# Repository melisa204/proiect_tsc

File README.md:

# TSC-Project

## BOM (Bill Of Materials)

| Component  | Supplier Link | Datasheet |
|------------|---------------|-----------|
| 112A-TAAR-R03 | [Model](https://store.comet.srl.ro/Catalogue/Product/43497/) | [Datasheet](https://www.snapeda.com/parts/112A-TAAR-R03/Attend/datasheet/) |
| 744043680 | [Model](https://ro.mouser.com/ProductDetail/Wurth-Elektronik/744043680?qs=PGXP4M47uW6VkZq%252BkzjrHA%3D%3D) | [Datasheet](https://www.we-online.com/components/products/datasheet/744043680.pdf) |
| BD5229G-TR | [Model](https://componentsearchengine.com/part-view/BD5229G-TR/ROHM%20Semiconductor) | [Datasheet](https://fscdn.rohm.com/en/products/databook/datasheet/ic/power/voltage_detector/bd52xxg-e.pdf) |
| Capacitor 0402 | [Model](https://ro.mouser.com/c/passive-components/capacitors/ceramic-capacitors/?q=CC0402&srsltid=AfmBOoogjqwwed3xvp6V5-bfVkRuawirfMcnAC47L-UQdC3mnXJk097M) | [Datasheet](https://componentsearchengine.com/Datasheets/2/CC0402MRX5R5BB106.pdf) |
| CPH3225A | [Model](https://www.snapeda.com/parts/CPH3225A/Seiko+Instruments/view-part/?ref=snap) | [Datasheet](https://www.snapeda.com/parts/CPH3225A/Seiko%20Instruments/datasheet/) |
| Custom Button | [Model](https://industry.panasonic.com/global/en/products/control/switch/light-touch/number/evqpuj02k) | [Datasheet](https://industry.panasonic.com/global/en/downloads?tab=catalog&small_g_cd=203&part_no=EVQPUJ02K) |
| DS3231SN | [Model](https://www.snapeda.com/parts/DS3231SN%23/Analog+Devices/view-part/?ref=eda) | [Datasheet](https://www.snapeda.com/parts/DS3231SN%23/Analog%20Devices/datasheet/) |
| ESP32 WROVER 0805 Capacitor | [Model](https://componentsearchengine.com/part-view/SD0805S020S1R0/Kyocera%20AVX) | [Datasheet]() |
| ESP32 WROVER BME680 Sensor | [Model](https://www.snapeda.com/parts/BME680/Bosch/view-part/?welcome=home) | [Datasheet](https://www.bosch-sensortec.com/media/boschsensortec/downloads/datasheets/bst-bme680-ds001.pdf) |
| ESP32 WROVER MCP73831 Power Management | [Model](https://www.snapeda.com/parts/BME680/Bosch/view-part/?welcome=home) | [Datasheet](https://www.snapeda.com/parts/MCP73831T-2ACI/OT/Microchip/datasheet/) |
| ESP32C6 Varistor 1812 | [Model](https://ro.mouser.com/ProductDetail/EPCOS-TDK/B72520T0350K062?qs=dEfas%2FXlABIszF52uu7vrg%3D%3D) | [Datasheet](https://ro.mouser.com/ProductDetail/EPCOS-TDK/B72520T0350K062?qs=dEfas%2FXlABIszF52uu7vrg%3D%3D&srsltid=AfmBOoq4QYIa9SsFxPeCqCK4SAxNo8l_QYsiO3XkER-r9cuptx7tEupO) |
| ESP32C6 WROOM-1-N8| [Model](https://www.snapeda.com/parts/ESP32-C6-WROOM-1-N8/Espressif+Systems/view-part/?ref=eda) | [Datasheet](https://www.snapeda.com/parts/ESP32-C6-WROOM-1-N8/Espressif%20Systems/datasheet/) |
| FH34SRJ-24S-0.5SH | [Model](https://ro.mouser.com/ProductDetail/Hirose-Connector/FH34SRJ-24S-0.5SH99?qs=vcbW%252B4%252BSTIpKBl5ap9J8Fw%3D%3D) | [Datasheet](https://www.snapeda.com/parts/FH34SRJ-24S-0.5SH(99)/Hirose%20Connector/datasheet/) |
| LED Chip 0603 | [Model](https://www.snapeda.com/parts/KP-1608SURCK/Kingbright/view-part/?ref=search&t=LED%200603) | [Datasheet](https://www.snapeda.com/parts/KP-1608SURCK/Kingbright/datasheet/) |
| MAX17048G+T10 | [Model](https://www.snapeda.com/parts/MAX17048G+T10/Analog+Devices/view-part/?ref=eda) | [Datasheet](https://www.snapeda.com/parts/MAX17048G+T10/Analog%20Devices/datasheet/) |
| MBR0530 Schottky Diode | [Model](https://www.snapeda.com/parts/MBR0530/Onsemi/view-part/?ref=snap) | [Datasheet](https://www.snapeda.com/parts/MBR0530/ON%20Semiconductor/datasheet/) |
| PGB1010603MR | [Model](https://www.snapeda.com/parts/PGB1010603MR/Littelfuse/view-part/?ref=eda) | [Datasheet](https://www.snapeda.com/parts/PGB1010603MR/Littelfuse%20Inc./datasheet/) |
| QWIIC Connector | [Model](https://www.snapeda.com/parts/PRT-14417/SparkFun/view-part/) | [Datasheet](https://www.snapeda.com/parts/PRT-14417/SparkFun%20Electronics/datasheet/) |
| RCL CPOL 3528 | [Model](https://www.snapeda.com/parts/CPH3225A/Seiko+Instruments/view-part/?ref=eda) | [Datasheet](https://s3.amazonaws.com/snapeda/datasheet/TAJB475K025RNJ_AVX.pdf) |
| Resistor 0402 | [Model](https://grabcad.com/library/resistor-0402-1) | [Datasheet](https://www.yageo.com/upload/media/product/products/datasheet/rchip/PYu-RC_Group_51_RoHS_L_12.pdf) |
| SI1308EDL-T1-GE3 MOSFET | [Model](https://www.snapeda.com/parts/SI1308EDL-T1-GE3/Vishay+Siliconix/view-part/?welcome=home&ref=eda) | [Datasheet](https://www.snapeda.com/parts/SI1308EDL-T1-GE3/Vishay%20Siliconix/datasheet/) |
| SJ | [Model](https://grabcad.com/library/solder-jumpers-1) | [Datasheet]() |
| USB4110-GF-A | [Model](https://componentsearchengine.com/part-view/USB4110-GF-A/GCT%20(GLOBAL%20CONNECTOR%20TECHNOLOGY)) | [Datasheet](https://gct.co/files/drawings/usb4110.pdf) |
| USBLC6-2SC6Y | [Model](https://www.snapeda.com/parts/USBLC6-2SC6Y/STMicroelectronics/view-part/?welcome=home&ref=eda) | [Datasheet](https://www.snapeda.com/parts/USBLC6-2SC6Y/STMicroelectronics/datasheet/) |
| W25Q512JVEIQ | [Model](https://www.snapeda.com/parts/W25Q512JVEIQ/Winbond+Electronics/view-part/?ref=eda) | [Datasheet](https://www.winbond.com/resource-files/W25Q512JV%20SPI%20RevB%2006252019%20KMS.pdf) |
| XC6220A331MR-G | [Model](https://componentsearchengine.com/part-view/XC6220A331MR-G/Torex) | [Datasheet](https://product.torexsemi.com/system/files/series/xc6220.pdf) |

## Power Consumption Estimation

## Hardware Description  

1. Microcontroller – ESP32-C6-WROOM-1-N8
The ESP32-C6 serves as the main processing unit, managing overall system operations, interfacing with
sensors and external modules, and overseeing power management tasks.
Architecture: 32-bit RISC-V
Clock Speed: 160 MHz
Wireless Connectivity: Wi-Fi 6 (2.4 GHz), Bluetooth 5.0

3. Power Management & Battery Battery Type: Li-Po (Lithium Polymer)
Capacity: 3.7V, 1800mAh
Charging Circuit: MCP73831T
Input Voltage: 5V via USB-C
Protection Features: Overcharge and deep discharge protection
Voltage Regulator: LDO regulator ensures a stable 3.3V power supply to all components.

4. Display - E-Paper (E-Ink) Screen
Size: 7.5 inches
Resolution: 800x480 pixels
Communication Interface: SPI

5. SD Card Module
Type: MicroSD (Supports FAT32)
Interface: SPI

6. External NOR Flash
Capacity: 64MB
Interface: SPI

7. Environmental Sensor - BME688
Functions: Measures temperature, humidity, air pressure, and gas levels.
Communication Interface: I2C 

8. Real-Time Clock (RTC) - DS3231SN
Functionality: Maintains time and date even when the system is powered off.
Communication Interface: I2C 

9. USB-C Connector & ESD Protection
Functionality: Provides power input and data transfer capability.
Protection: Integrated ESD protection and Schottky diode for reverse polarity safety. 

10. Buttons & User Input
Tactile Push Buttons

11. Communication Interfaces
GPIO: Used for button controls and general I/O operations.
SPI: Used for SD card, external flash memory, and e-paper display.
I2C: Used for the BME688 environmental sensor and DS3231SN RTC module.
UART: Used for debugging and serial communication.
Wi-Fi & Bluetooth: Provided by ESP32-C6, allowing wireless connectivity.

## Power Consumption Estimation

| Component                | Current Draw (mA) | Voltage (V) | Power (mW) |
|--------------------------|------------------|-------------|------------|
| ESP32-C6 (Wi-Fi active)  |200               |3.3          |660
| E-Paper Display (Updating)               | 40               | 3.3         | 132        |
| BME688 Sensor (Measuring)| 3.1              | 3.3         | 10.23      |
| RTC Module (Active)      | 0.15             | 3.3         | 0.495      |
| SD Card (Active)         | 50               | 3.3         | 165        |
| Externar NOR Flash       | 25               | 3.3         | 82.5       |
| Total Estimated Power Consumption               | ~318.5mA         | 3.3         | 1050.72    |

## ESP32-C6 Pin Mapping  

| Component                | ESP32-C6 Pin(s) | Interface | Purpose |
|--------------------------|----------------|-----------|---------|
| **E-Paper Display**      | IO7 (MOSI), IO6 (SCK), IO10 (CS), IO5 (DC), IO23 (RST), IO3 (BUSY) | SPI | Transfers image data to the display and controls its state. |
| **MicroSD Card**         | IO7 (MOSI), IO6 (SCK), IO4 (SS_SD), IO2 (MISO) | SPI | Allows storage and retrieval of e-book files. |
| **Environmental Sensor (BME688)** | IO21 (SDA), IO22 (SCL) | I2C | Reads temperature, humidity, pressure, and air quality data. |
| **RTC Module (DS3231)**  | IO21 (SDA), IO22 (SCL), IO18 (RST), IO1 (32KHz), IO0 (INT_RTC) | I2C | Keeps track of time even when ESP32 is off. |
| **External NOR Flash**   | IO11 (CS), IO6 (SCK), IO2 (MISO), IO7 (MOSI) | SPI | Provides additional storage for application data. |
| **Battery Monitoring**   | IO21 (SDA), IO22 (SCL) | I2C | Reads battery voltage and charge status. |
| **USB-C Connection**     | GPIOs through voltage regulation | USB | Powers and programs the ESP32-C6. |
| **Control Buttons**      | IO9 (BOOT), IO15 (CHANGE), EN (RESET) | GPIO | User input for device interactions. |
|

## Additional Design Notes
### Footprint Adjustments
Diode (SMD-Hole): The original footprint had pad holes that were too small, which would have caused soldering issues.
The pad size was updated to 35mil x 190mil to ensure manufacturability and a reliable electrical connection.

U4 – MAX17048G+T10: The VBAT power trace was designed with a width of 0.3mm, based on implementation constraints
However, the footprint had pin widths of only 0.27mm, resulting in asymmetry and inconsistent routing. The pin sizes
were adjusted to match the trace width and maintain design symmetry.

### Routing & Ground Plane
Power traces were routed only on the top layer, which required the use of approximately 110 vias to allow for
signal routing on the bottom layer.

The ground plane (GND) was added after routing was completed, applied to both top and bottom layers to ensure
low-impedance grounding and reduced EMI.

### Component Placement
Test pads (TPs) were placed near the edges of the board and close to major components for easy debugging access.

### Schematic & 3D Model Issues
After completing the routing process, updates to the 3D models led to pin order reversals in certain 2-pin components, 
which disrupted existing connections. The issue was resolved by rotating the affected components 180° and re-aligning their 
pins accordingly.

### Enclosure & 3D Integration
3D components were imported using two methods, depending on how frequently each part appeared in the schematic.

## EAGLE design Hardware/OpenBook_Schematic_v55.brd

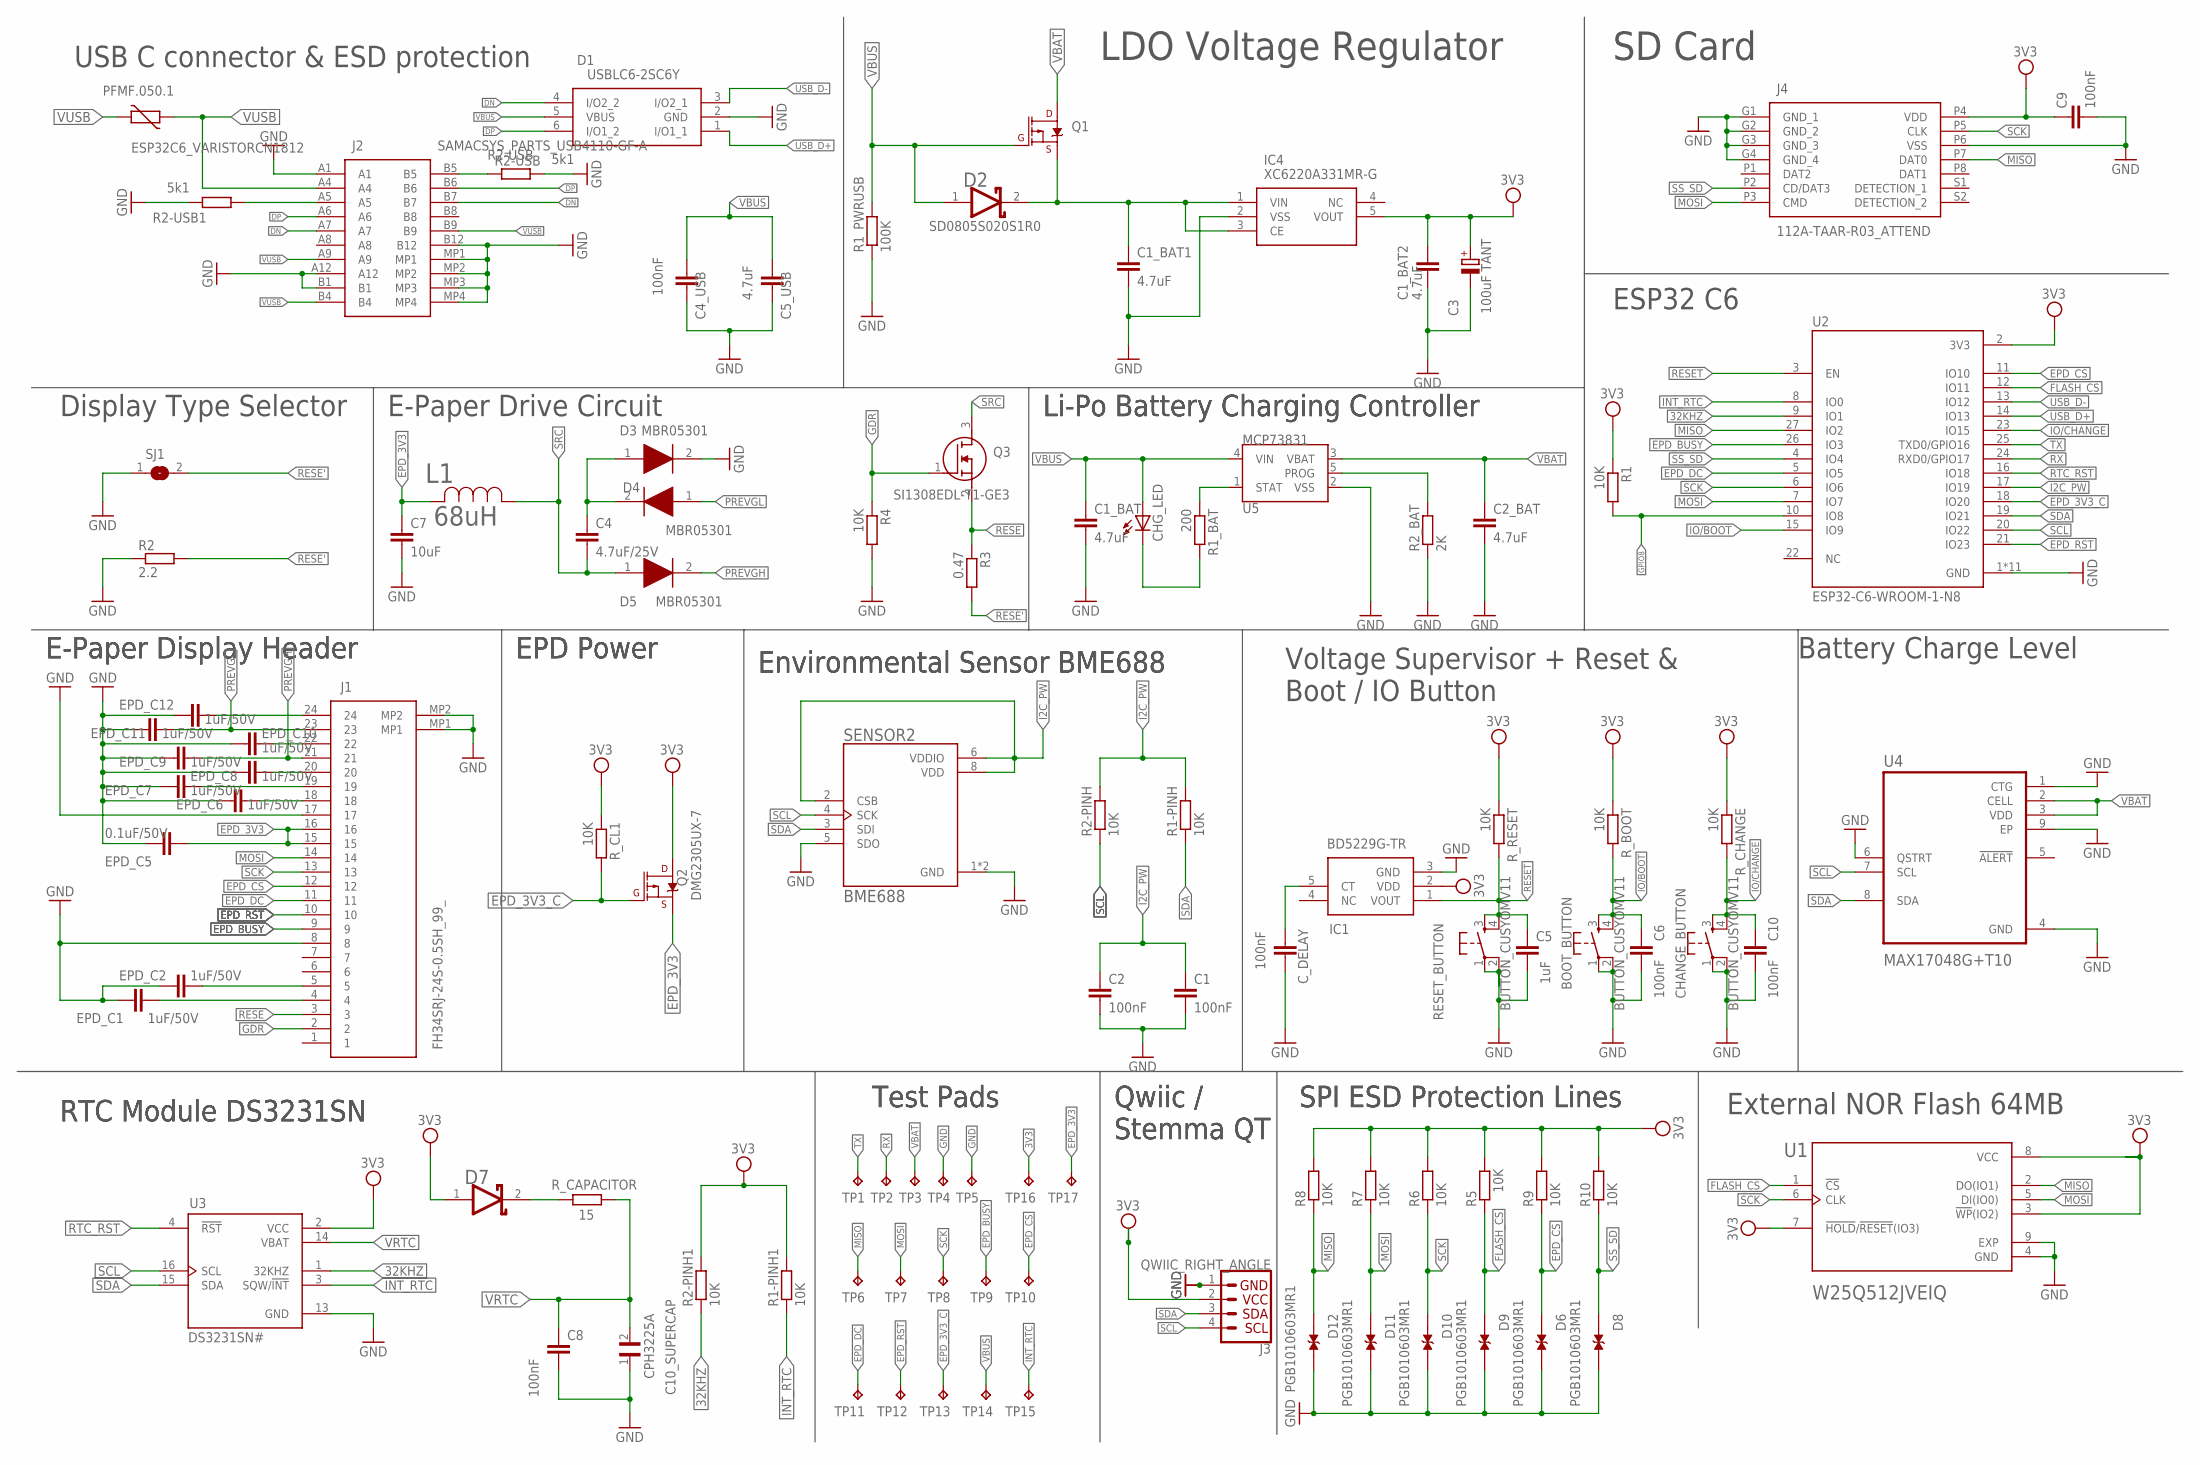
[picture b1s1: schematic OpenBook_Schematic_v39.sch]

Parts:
BOOT_BUTTON: BUTTON_CUSYOMV11; MYBUTTON
C1, C2, C4_USB, C6, C8, C9, C10: 100nF; EAGLE-LTSPICE_C0402
C1_BAT, C1_BAT1, C1_BAT2, C2_BAT, C5_USB: 4.7uF; EAGLE-LTSPICE_C0402
C3: 100uF TANT; RCL_CT3528
C4: 4.7uF/25V; EAGLE-LTSPICE_C0402
C5: 1uF; EAGLE-LTSPICE_C0402
C7: 10uF; EAGLE-LTSPICE_C0402
C10_SUPERCAP: CPH3225A; CAPCP3225X100N
CHANGE_BUTTON: BUTTON_CUSYOMV11; MYBUTTON
CHG_LED: ADAFRUIT_LEDCHIP-LED0603; ADAFRUIT_CHIP-LED0603
C_DELAY: 100nF; EAGLE-LTSPICE_C0402
D1: USBLC6-2SC6Y; SOT95P280X145-6N
D2, D7: SD0805S020S1R0; ESP32_WROVER_AVX---SD0805S020S1R0_AVX_SD0805S020S1R0_0
D3, D4, D5: MBR05301; SOD3716X135N
D6, D8, D9, D10, D11, D12: PGB1010603MR1; DIOC1608X36N
EPD_C1, EPD_C2, EPD_C6, EPD_C7, EPD_C8, EPD_C9, EPD_C10, EPD_C11, EPD_C12: 1uF/50V; EAGLE-LTSPICE_C0402
EPD_C5: 0.1uF/50V; EAGLE-LTSPICE_C0402
IC1: BD5229G-TR; SOT95P280X125-5N
IC4: XC6220A331MR-G; SOT95P280X120-5N
J1: FH34SRJ-24S-0.5SH_99_; FH34SRJ24S05SH99
J2: SAMACSYS_PARTS_USB4110-GF-A; SAMACSYS_PARTS_USB4110GFA
J3: QWIIC_RIGHT_ANGLE; JST04_1MM_RA
J4: 112A-TAAR-R03_ATTEND; 112ATAARR03ATTEND
L1: 68uH; IND_4828-WE-TPC_WRE
PFMF.050.1: ESP32C6_VARISTORCN1812; ESP32C6_VARISTOR_CT/CN1812
Q1, Q2: 20V/4.2A/52mΩ/1.4W; ESP32_WROVER_SPARKFUN-DISCRETESEMI_SOT23-3
Q3: SI1308EDL-T1-GE3; SOT65P210X110-3N
R1, R1-PINH, R1-PINH1, R2-PINH, R2-PINH1, R4, R5, R6, R7, R8, R9, R10: 10K; ESP32_WROVER_EAGLE-LTSPICE_R0402
R1_BAT: 200; ESP32_WROVER_EAGLE-LTSPICE_R0402
R1_PWRUSB: 100K; ESP32_WROVER_EAGLE-LTSPICE_R0402
R2: 2.2; ESP32_WROVER_EAGLE-LTSPICE_R0402
R2-USB, R2-USB1: 5k1; ESP32_WROVER_EAGLE-LTSPICE_R0402
R2_BAT: 2K; ESP32_WROVER_EAGLE-LTSPICE_R0402
R3: 0.47; ESP32_WROVER_EAGLE-LTSPICE_R0402
RESET_BUTTON: BUTTON_CUSYOMV11; MYBUTTON
R_BOOT: 10K; ESP32_WROVER_EAGLE-LTSPICE_R0402
R_CAPACITOR: 15; ESP32_WROVER_EAGLE-LTSPICE_R0402
R_CHANGE: 10K; ESP32_WROVER_EAGLE-LTSPICE_R0402
R_CL1: 10K; ESP32_WROVER_EAGLE-LTSPICE_R0402
R_RESET: 10K; ESP32_WROVER_EAGLE-LTSPICE_R0402
SENSOR2: BME688; ESP32_WROVER_BME680_PSON80P300X300X100-8N
SJ1: SJ
TP1, TP2, TP3, TP4, TP5, TP6, TP7, TP8, TP9, TP10, TP11, TP12, TP13, TP14, TP15, TP16, TP17: TPTP20R; TP20R
U1: W25Q512JVEIQ; SON127P600X800X80-9N
U2: ESP32-C6-WROOM-1-N8; XCVR_ESP32-C6-WROOM-1-N8
U3: DS3231SN#; SOIC127P1032X265-16N
U4: MAX17048G+T10; SON50P200X200X80-9N
U5: MCP73831; ESP32_WROVER_SPARKFUN-IC-POWER_SOT23-5

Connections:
3V3: C1_BAT2.1, C3.+, C9.1, D7.1 (ANODE), IC1.2 (VDD), IC4.5 (VOUT), J3.2, J4.P4 (VDD), Q2.1 (D), R1.1, R1-PINH1.2, R2-PINH1.2, R5.2, R6.2, R7.2, R8.2, R9.2, R10.2, R_BOOT.1, R_CHANGE.1, R_CL1.1, R_RESET.1, TP16.TP, U1.3 (!WP!(IO2)), U1.7 (!HOLD!/!RESET!(IO3)), U1.8 (VCC), U2.2 (3V3), U3.2 (VCC)
32KHZ: R2-PINH1.1, U2.9 (IO1), U3.1 (32KHZ)
DN: D1.4 (I/O2_2), J2.A7, J2.B7
DP: D1.6 (I/O1_2), J2.A6, J2.B6
EPD_3V3: C7.1, EPD_C5.1, J1.15, J1.16, L1.2, Q2.3 (S), TP17.TP
EPD_3V3_C: Q2.2 (G), R_CL1.2, TP13.TP, U2.18 (IO20)
EPD_BUSY: J1.9, TP9.TP, U2.26 (IO3)
EPD_CS: D6.1, J1.12, R9.1, TP10.TP, U2.11 (IO10)
EPD_DC: J1.11, TP11.TP, U2.5 (IO5)
EPD_RST: J1.10, TP12.TP, U2.21 (IO23)
FLASH_CS: D9.1, R5.1, U1.1 (!CS), U2.12 (IO11)
GDR: J1.2, Q3.1 (G), R4.1
GND: BOOT_BUTTON.1, BOOT_BUTTON.2, C1.2, C1_BAT.2, C1_BAT1.2, C1_BAT2.2, C2.2, C2_BAT.2, C3.-, C4_USB.2, C5.2, C5_USB.2, C6.2, C7.2, C8.2, C9.2, C10.2, C10_SUPERCAP.1, CHANGE_BUTTON.1, CHANGE_BUTTON.2, C_DELAY.2, D1.2 (GND), D3.2 (K), D6.2, D8.2, D9.2, D10.2, D11.2, D12.2, EPD_C1.2, EPD_C2.2, EPD_C5.2, EPD_C6.2, EPD_C7.2, EPD_C8.2, EPD_C9.2, EPD_C10.2, EPD_C11.2, EPD_C12.2, IC1.3 (GND), IC4.2 (VSS), J1.8, J1.17, J1.MP1, J1.MP2, J2.A1, J2.A12, J2.B1, J2.B12, J2.MP1, J2.MP2, J2.MP3, J2.MP4, J3.1, J4.G1 (GND_1), J4.G2 (GND_2), J4.G3 (GND_3), J4.G4 (GND_4), J4.P6 (VSS), R1_PWRUSB.1, R2.1, R2-USB.2, R2-USB1.1, R2_BAT.1, R4.2, RESET_BUTTON.1, RESET_BUTTON.2, SENSOR2.1 (GND), SENSOR2.5 (SDO), SENSOR2.7 (GND), SJ1.1, TP4.TP, TP5.TP, U1.4 (GND), U1.9 (EXP), U2.1 (GND), U2.28 (GND), U2.29_1 (GND), U2.29_2 (GND), U2.29_3 (GND), U2.29_4 (GND), U2.29_5 (GND), U2.29_6 (GND), U2.29_7 (GND), U2.29_8 (GND), U2.29_9 (GND), U3.13 (GND), U4.1 (CTG), U4.4 (GND), U4.6 (QSTRT), U4.9 (EP), U5.2 (VSS)
GPIO8: R1.2, U2.10 (IO8)
I2C_PW: C1.1, C2.1, R1-PINH.2, R2-PINH.2, SENSOR2.2 (CSB), SENSOR2.6 (VDDIO), SENSOR2.8 (VDD), U2.17 (IO19)
INT_RTC: R1-PINH1.1, TP15.TP, U2.8 (IO0), U3.3 (SQW/!INT)
IO/BOOT: BOOT_BUTTON.3, BOOT_BUTTON.4, C6.1, R_BOOT.2, U2.15 (IO9)
IO/CHANGE: C10.1, CHANGE_BUTTON.3, CHANGE_BUTTON.4, R_CHANGE.2, U2.23 (IO15)
MISO: D12.1, J4.P7 (DAT0), R8.1, TP6.TP, U1.2 (DO(IO1)), U2.27 (IO2)
MOSI: D11.1, J1.14, J4.P3 (CMD), R7.1, TP7.TP, U1.5 (DI(IO0)), U2.7 (IO7)
unnamed: C_DELAY.1, IC1.5 (CT)
unnamed: EPD_C6.1, J1.18
unnamed: J2.A5, R2-USB1.2
unnamed: EPD_C1.1, J1.4
unnamed: EPD_C2.1, J1.5
unnamed: EPD_C7.1, J1.19
unnamed: EPD_C8.1, J1.20
unnamed: R1_BAT.1, U5.1 (STAT)
unnamed: EPD_C10.1, J1.22
unnamed: CHG_LED.C, R1_BAT.2
unnamed: J2.B5, R2-USB.1
unnamed: EPD_C12.1, J1.24
unnamed: C4.1, D3.1 (A), D4.2 (K)
unnamed: R2_BAT.2, U5.5 (PROG)
unnamed: C1_BAT1.1, D2.2 (CATHODE), IC4.1 (VIN), IC4.3 (CE), Q1.3 (S)
unnamed: D7.2 (CATHODE), R_CAPACITOR.2
PREVGH: D5.2 (K), EPD_C9.1, J1.21
PREVGL: D4.1 (A), EPD_C11.1, J1.23
RESE: J1.3, Q3.2 (S), R3.1
RESE': R2.2, R3.2, SJ1.2
RESET: C5.1, IC1.1 (VOUT), RESET_BUTTON.3, RESET_BUTTON.4, R_RESET.2, U2.3 (EN)
RTC_RST: U2.16 (IO18), U3.4 (!RST)
RX: TP2.TP, U2.24 (RXD0/GPIO17)
SCK: D10.1, J1.13, J4.P5 (CLK), R6.1, TP8.TP, U1.6 (CLK), U2.6 (IO6)
SCL: J3.4, R2-PINH.1, SENSOR2.4 (SCK), U2.20 (IO22), U3.16 (SCL), U4.7 (SCL)
SDA: J3.3, R1-PINH.1, SENSOR2.3 (SDI), U2.19 (IO21), U3.15 (SDA), U4.8 (SDA)
SRC: C4.2, D5.1 (A), L1.1, Q3.3 (D)
SS_SD: D8.1, J4.P2 (CD/DAT3), R10.1, U2.4 (IO4)
TX: TP1.TP, U2.25 (TXD0/GPIO16)
USB_D+: D1.1 (I/O1_1), U2.14 (IO13)
USB_D-: D1.3 (I/O2_1), U2.13 (IO12)
VBAT: C2_BAT.1, Q1.1 (D), TP3.TP, U4.2 (CELL), U4.3 (VDD), U5.3 (VBAT)
VBUS: C1_BAT.1, C4_USB.1, C5_USB.1, CHG_LED.A, D1.5 (VBUS), D2.1 (ANODE), Q1.2 (G), R1_PWRUSB.2, TP14.TP, U5.4 (VIN)
VRTC: C8.1, C10_SUPERCAP.2, R_CAPACITOR.1, U3.14 (VBAT)
VUSB: J2.A4, J2.A9, J2.B4, J2.B9, PFMF.050.1.1, PFMF.050.1.2

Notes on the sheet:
USB C connector & ESD protection
LDO Voltage Regulator
SD Card
ESP32 C6
RTC Module DS3231SN
Test Pads
Qwiic / Stemma QT
SPI ESD Protection Lines
External NOR Flash 64MB
Battery Charge Level
Voltage Supervisor + Reset & Boot / IO Button
Environmental Sensor BME688
EPD Power
E-Paper Display Header
Li-Po Battery Charging Controller
E-Paper Drive Circuit
Display Type Selector

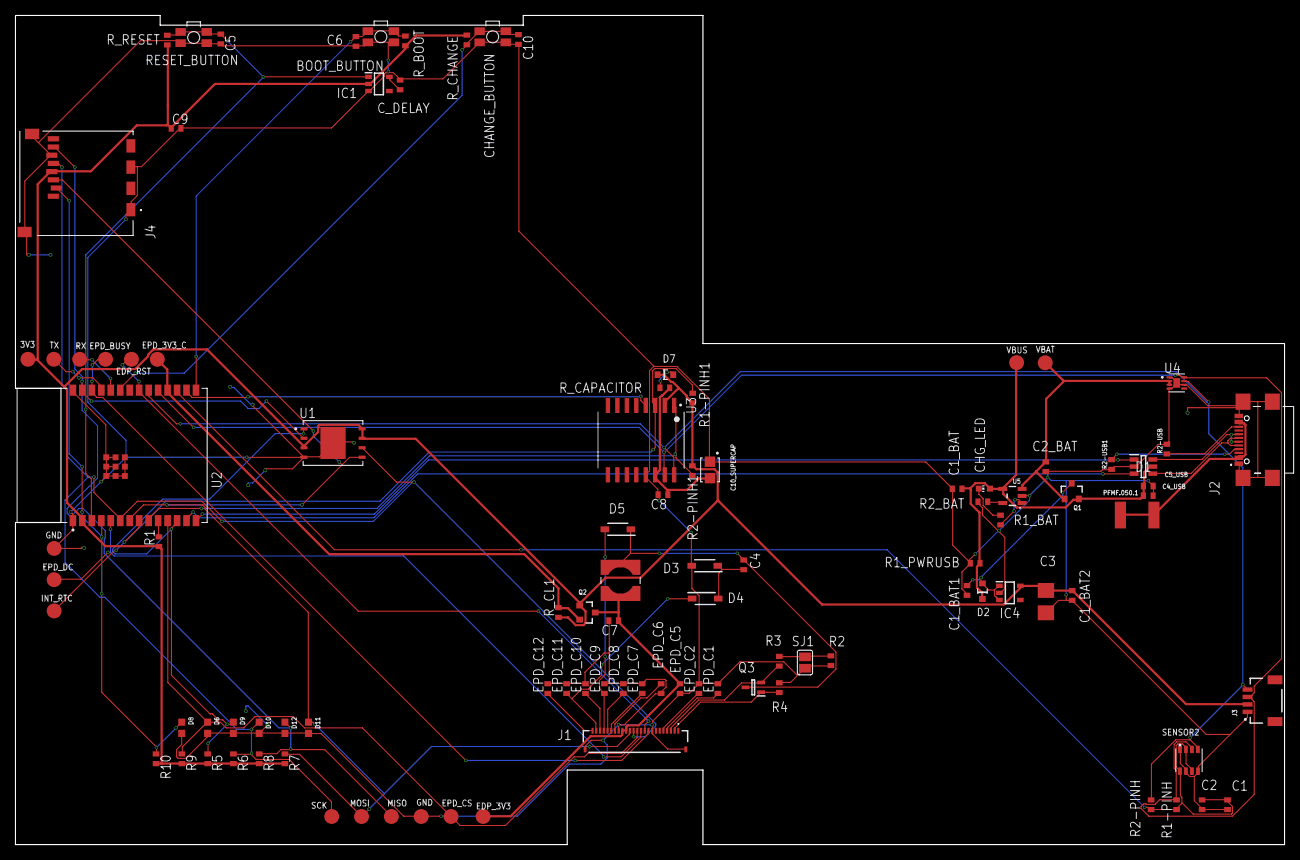
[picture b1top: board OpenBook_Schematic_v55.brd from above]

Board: 2 copper layers, 170.2 x 111.2 mm, 103 parts (0 on the bottom side), 55 nets.

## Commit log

2025-04-06 Create LICENSE

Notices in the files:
parts and their libraries:
DeskAssistant v19 v1: COPYRIGHT: Copyright (C) 2024 Ultra Librarian. All rights reserved.
